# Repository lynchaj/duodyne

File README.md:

# duodyne
* duodyne is a hobbyist retrocomputer system comprised of modules on a system bus.  It is specifically designed to run RomWBW, however, provides support for multiple processor architectures and has a flexible and expandable system bus.

* The system bus is designed to support multiple vintage or retro computer processor architectures such as those from Intel, Zilog, Motorola, Mostek, etc.  The Z80 is the primary CPU used to develop the initial round of peripherals.

* Duodyne borrows heavily from previous computer systems.  The form factor is similar to S-100 and VME.  The bus is electrically is derived from ECB with many extensions to support other processor architectures and improved power distribution.  There are multiple pins for 5V and ground.  +12V and -12V are supported.  3.3V and other values can be derived on board using voltage regulators.

* The plan for the system is to have balance between functionality and complexity.  A single function per board has good distribution and easy expansion but leads to many boards and a large backplane which can lead to electrical and signal distribution issues.  However, full integration into a single board computer reduces complexity somewhat but can make expansion difficult.  

* Duoodyne's bus based approach with a generous board form factor allows for a blend of integration and distribution of two or more functions per board leading to a smaller overall backplane yet retaining flexibility for easy expansion.

* The duodyne core system is defined as an 4-slot or 8-slot backplane, a Z80 or other processor (currently, Z80, 65C816, and TMS9995 are supported), and a ROMRAM board.  The ROMRAM memory board assumes an 8-bit data bus so CPU's with larger data busses may require dedicated memory boards.  The Z80 processor includes a debugging serial port for console access.  The boot ROM is included on the ROMRAM board.

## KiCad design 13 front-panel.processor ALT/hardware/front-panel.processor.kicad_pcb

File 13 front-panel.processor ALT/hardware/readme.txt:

The 4-slot backplane is for the initial prototyping phase of the system.  It can also be used for creating a minimum sized unit.  

The minimum boards for a complete system are: 1) backplane, 2) processor, and 3) ROM & RAM; assumes using processor debug serial port as console

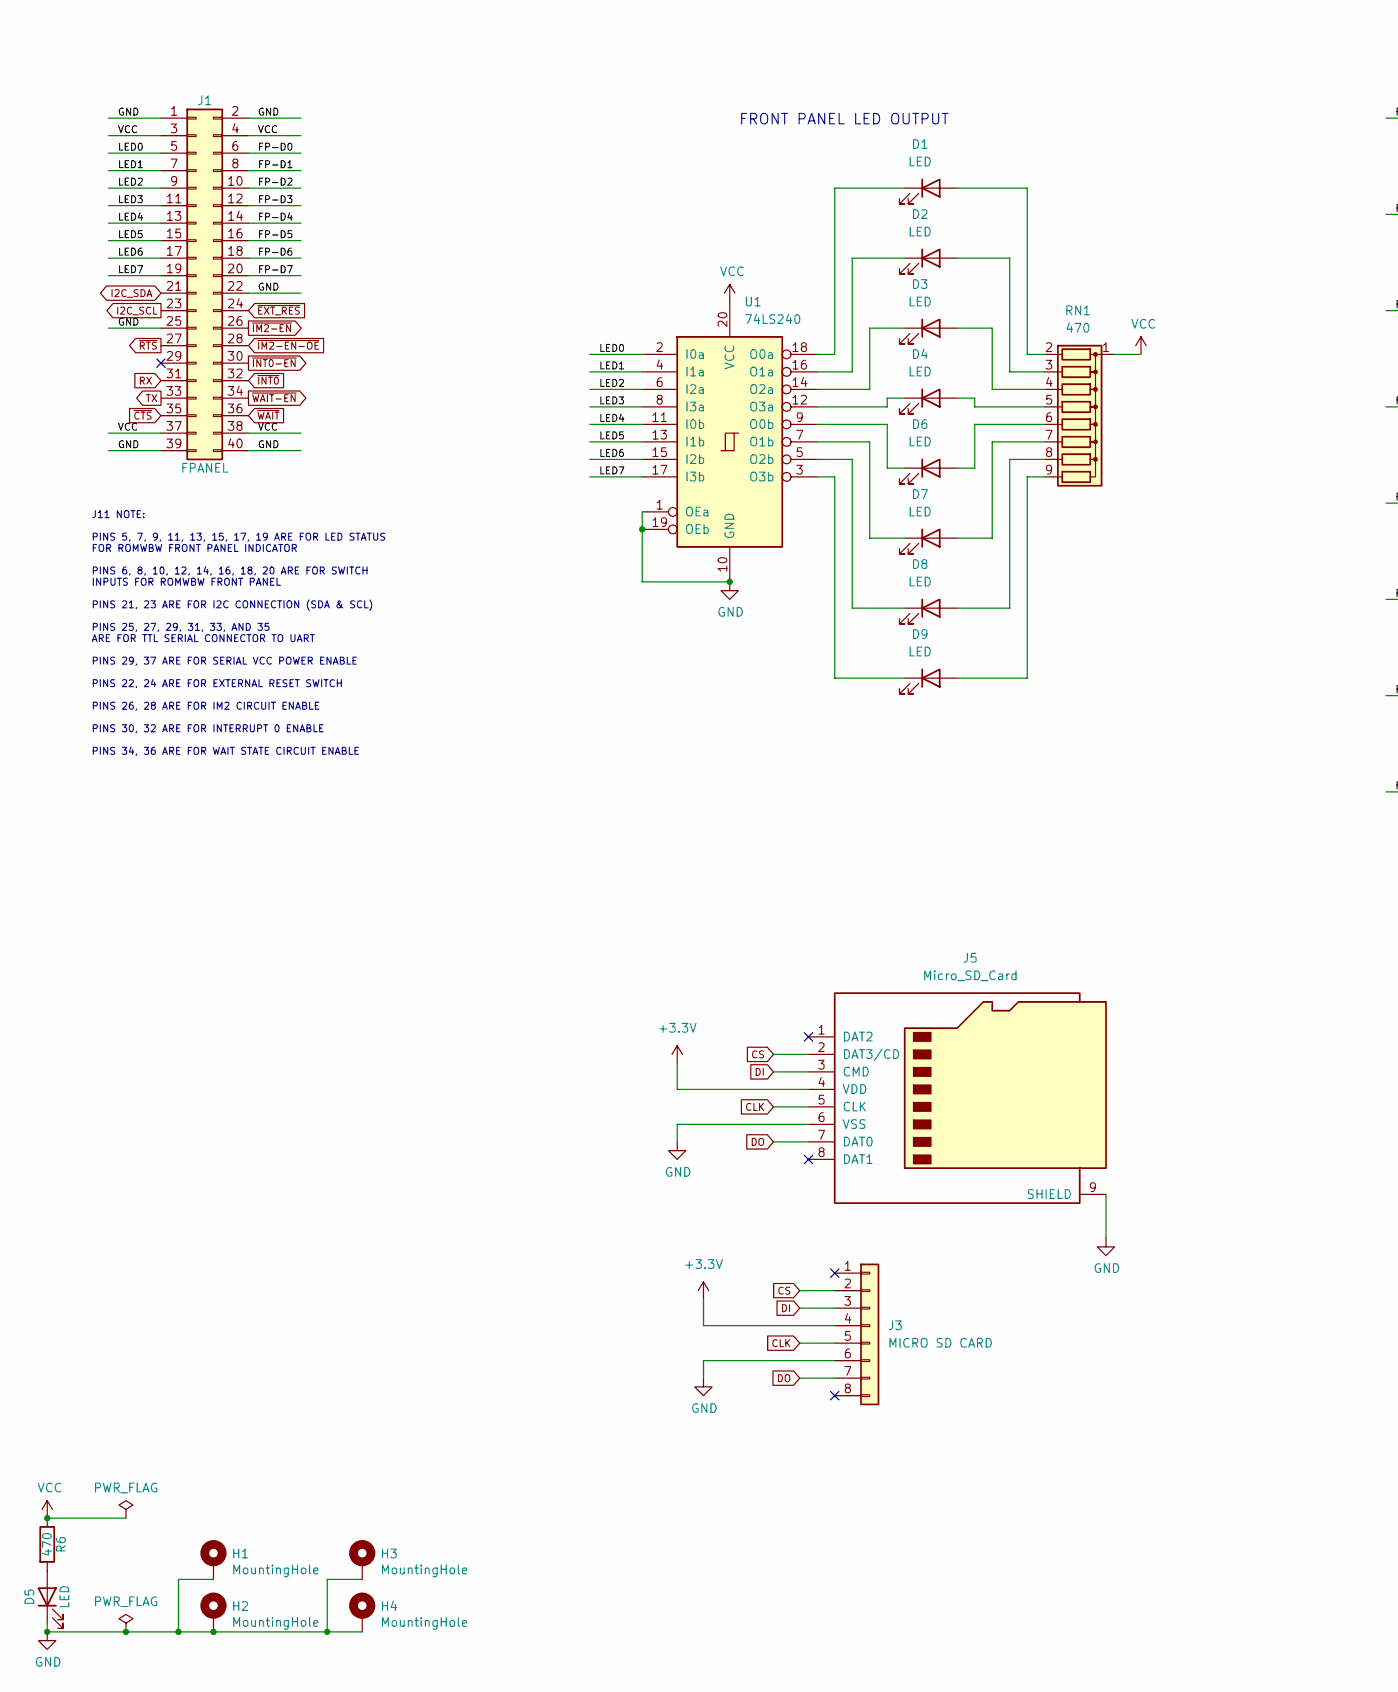
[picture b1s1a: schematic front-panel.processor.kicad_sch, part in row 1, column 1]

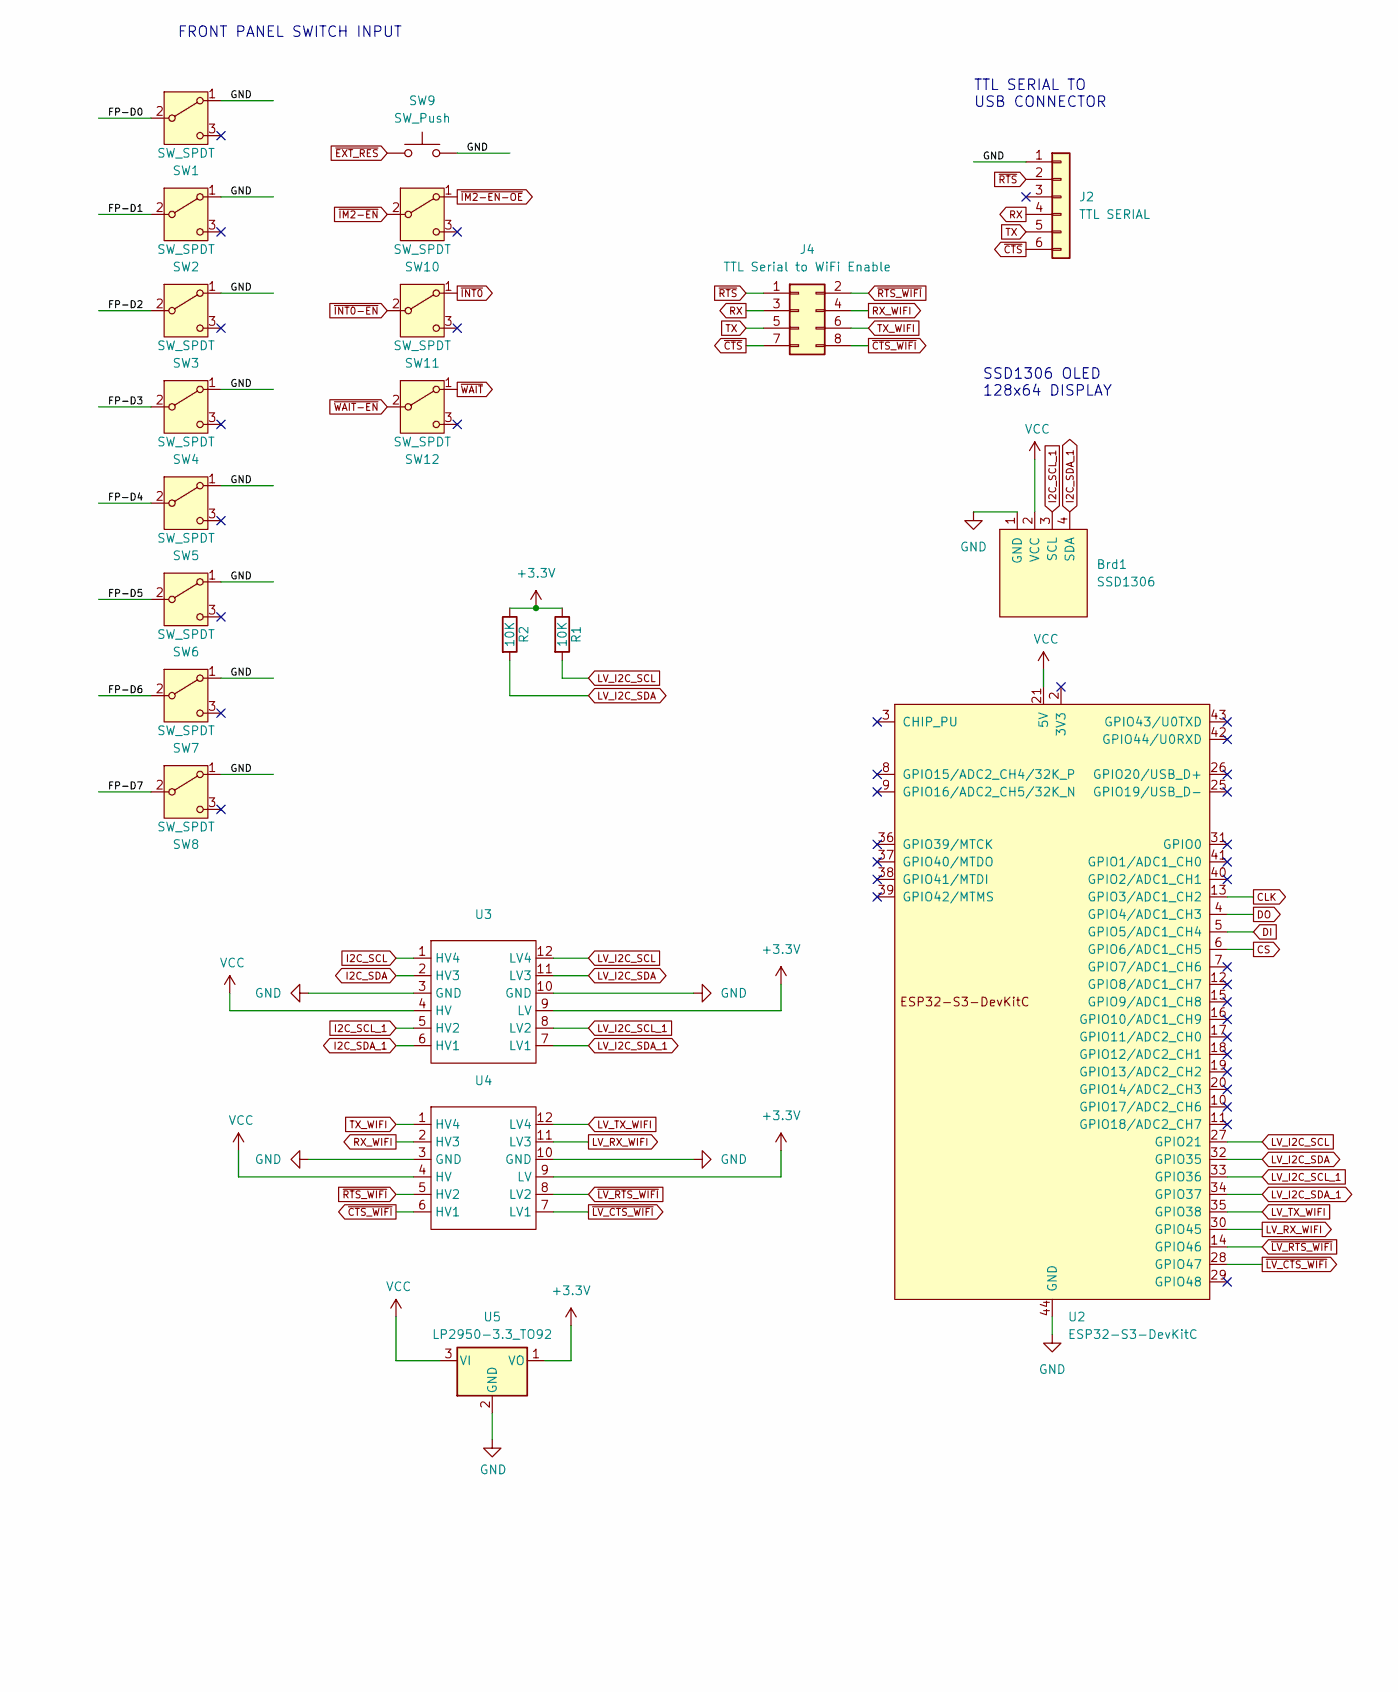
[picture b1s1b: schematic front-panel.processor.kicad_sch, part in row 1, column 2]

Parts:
Brd1: SSD1306; 128x64OLED
D1, D2, D3, D4, D5, D6, D7, D8, D9: LED; LED_D3.0mm
H1, H2, H3, H4: MountingHole; MountingHole_3.2mm_M3_Pad
J1: FPANEL; IDC-Header_2x20_P2.54mm_Horizontal
J2: TTL SERIAL; PinHeader_1x06_P2.54mm_Vertical
J3: MICRO SD CARD; PinSocket_1x08_P2.54mm_Vertical
J4: TTL Serial to WiFi Enable; PinHeader_2x04_P2.54mm_Vertical
J5: Micro_SD_Card; SD_Hirose_DM1AA_SF_PEJ82
R1, R2: 10K; R_Axial_DIN0207_L6.3mm_D2.5mm_P7.62mm_Horizontal
R6: 470; R_Axial_DIN0207_L6.3mm_D2.5mm_P7.62mm_Horizontal
RN1: 470; R_Array_SIP9
SW1, SW2, SW3, SW4, SW5, SW6, SW7, SW8, SW10, SW11, SW12: SW_SPDT; SW_Toggle_Blue_wSlots
SW9: SW_Push; SW_PUSH_6mm
U1: 74LS240; DIP-20_W7.62mm
U2: ESP32-S3-DevKitC; ESP32S3Devkit3Universal
U3, U4: HV-LV
U5: LP2950-3.3_TO92; TO-92_Inline

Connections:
+3.3V: J3.4, J5.4 (VDD), R1.1, R2.1, U3.9 (LV), U4.9 (LV), U5.1 (VO)
/FP-D0: J1.6, SW1.2 (B)
/FP-D1: J1.8, SW2.2 (B)
/FP-D2: J1.10, SW3.2 (B)
/FP-D3: J1.12, SW4.2 (B)
/FP-D4: J1.14, SW5.2 (B)
/FP-D5: J1.16, SW6.2 (B)
/FP-D6: J1.18, SW7.2 (B)
/FP-D7: J1.20, SW8.2 (B)
/LED0: J1.5, U1.2 (I0a)
/LED1: J1.7, U1.4 (I1a)
/LED2: J1.9, U1.6 (I2a)
/LED3: J1.11, U1.8 (I3a)
/LED4: J1.13, U1.11 (I0b)
/LED5: J1.15, U1.13 (I1b)
/LED6: J1.17, U1.15 (I2b)
/LED7: J1.19, U1.17 (I3b)
CLK: J3.5, J5.5 (CLK), U2.13 (GPIO3/ADC1_CH2)
CS: J3.2, J5.2 (DAT3/CD), U2.6 (GPIO6/ADC1_CH5)
DI: J3.3, J5.3 (CMD), U2.5 (GPIO5/ADC1_CH4)
DO: J3.7, J5.7 (DAT0), U2.4 (GPIO4/ADC1_CH3)
GND: Brd1.1 (GND), D5.1 (K), H1.1, H2.1, H3.1, H4.1, J1.1, J1.2, J1.22, J1.25, J1.39, J1.40, J2.1, J3.6, J5.6 (VSS), J5.9 (SHIELD), SW1.1 (A), SW2.1 (A), SW3.1 (A), SW4.1 (A), SW5.1 (A), SW6.1 (A), SW7.1 (A), SW8.1 (A), SW9.2, U1.1 (OEa), U1.10 (GND), U1.19 (OEb), U2.22 (GND), U2.23 (GND), U2.24 (GND), U2.44 (GND), U3.3 (GND), U3.10 (GND), U4.3 (GND), U4.10 (GND), U5.2 (GND)
I2C_SCL: J1.23, U3.1 (HV4)
I2C_SCL_1: Brd1.3 (SCL), U3.5 (HV2)
I2C_SDA: J1.21, U3.2 (HV3)
I2C_SDA_1: Brd1.4 (SDA), U3.6 (HV1)
LV_I2C_SCL: R1.2, U2.27 (GPIO21), U3.12 (LV4)
LV_I2C_SCL_1: U2.33 (GPIO36), U3.8 (LV2)
LV_I2C_SDA: R2.2, U2.32 (GPIO35), U3.11 (LV3)
LV_I2C_SDA_1: U2.34 (GPIO37), U3.7 (LV1)
LV_RX_WIFI: U2.30 (GPIO45), U4.11 (LV3)
LV_TX_WIFI: U2.35 (GPIO38), U4.12 (LV4)
unnamed: D1.2 (A), RN1.2 (R1)
unnamed: D1.1 (K), U1.18 (O0a)
unnamed: D2.2 (A), RN1.3 (R2)
unnamed: D2.1 (K), U1.16 (O1a)
unnamed: D3.2 (A), RN1.4 (R3)
unnamed: D3.1 (K), U1.14 (O2a)
unnamed: D4.2 (A), RN1.5 (R4)
unnamed: D4.1 (K), U1.12 (O3a)
unnamed: D5.2 (A), R6.2
unnamed: D6.2 (A), RN1.6 (R5)
unnamed: D6.1 (K), U1.9 (O0b)
unnamed: D7.2 (A), RN1.7 (R6)
unnamed: D7.1 (K), U1.7 (O1b)
unnamed: D8.2 (A), RN1.8 (R7)
unnamed: D8.1 (K), U1.5 (O2b)
unnamed: D9.2 (A), RN1.9 (R8)
unnamed: D9.1 (K), U1.3 (O3b)
RX: J1.31, J2.4, J4.3
RX_WIFI: J4.4, U4.2 (HV3)
TX: J1.33, J2.5, J4.5
TX_WIFI: J4.6, U4.1 (HV4)
VCC: Brd1.2 (VCC), J1.3, J1.4, J1.37, J1.38, R6.1, RN1.1 (common), U1.20 (VCC), U2.21 (5V), U3.4 (HV), U4.4 (HV), U5.3 (VI)
~CTS_WIFI: J4.8, U4.6 (HV1)
~CTS: J1.35, J2.6, J4.7
~EXT_RES: J1.24, SW9.1
~IM2-EN-OE: J1.28, SW10.1 (A)
~IM2-EN: J1.26, SW10.2 (B)
~INT0-EN: J1.30, SW11.2 (B)
~INT0: J1.32, SW11.1 (A)
~LV_CTS_WIFI: U2.28 (GPIO47), U4.7 (LV1)
~LV_RTS_WIFI: U2.14 (GPIO46), U4.8 (LV2)
~RTS_WIFI: J4.2, U4.5 (HV2)
~RTS: J1.27, J2.2, J4.1
~WAIT-EN: J1.34, SW12.2 (B)
~WAIT: J1.36, SW12.1 (A)

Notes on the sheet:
SSD1306 OLED 128x64 DISPLAY
FRONT PANEL LED OUTPUT
J11 NOTE: PINS 5, 7, 9, 11, 13, 15, 17, 19 ARE FOR LED STATUS FOR ROMWBW FRONT PANEL INDICATOR PINS 6, 8, 10, 12, 14, 16, 18, 20 ARE FOR SWITCH INPUTS FOR ROMWBW FRONT PANEL PINS 21, 23 ARE FOR I2C CONNECTION (SDA & SCL) PINS 25, 27, 29, 31, 33, AND 35 ARE FOR TTL SERIAL CONNECTOR TO UART PINS 29, 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
FRONT PANEL SWITCH INPUT
TTL SERIAL TO USB CONNECTOR

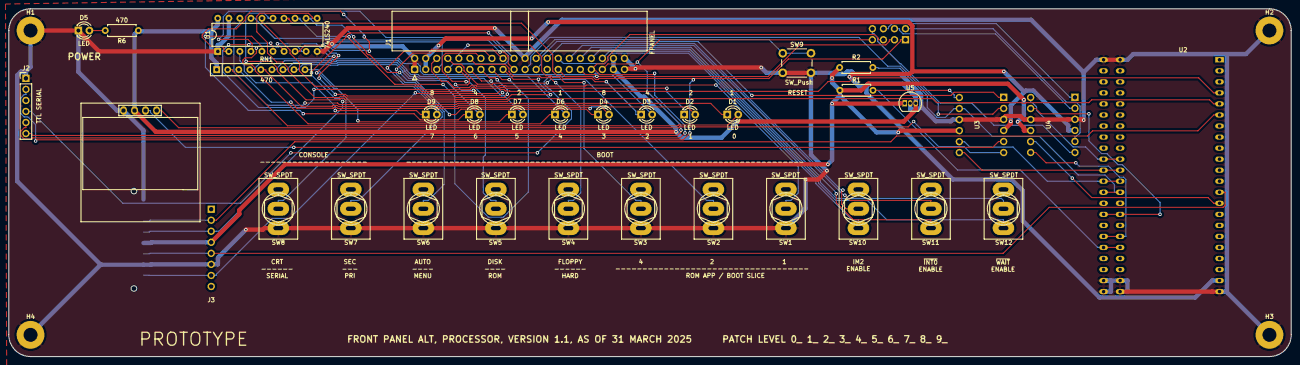
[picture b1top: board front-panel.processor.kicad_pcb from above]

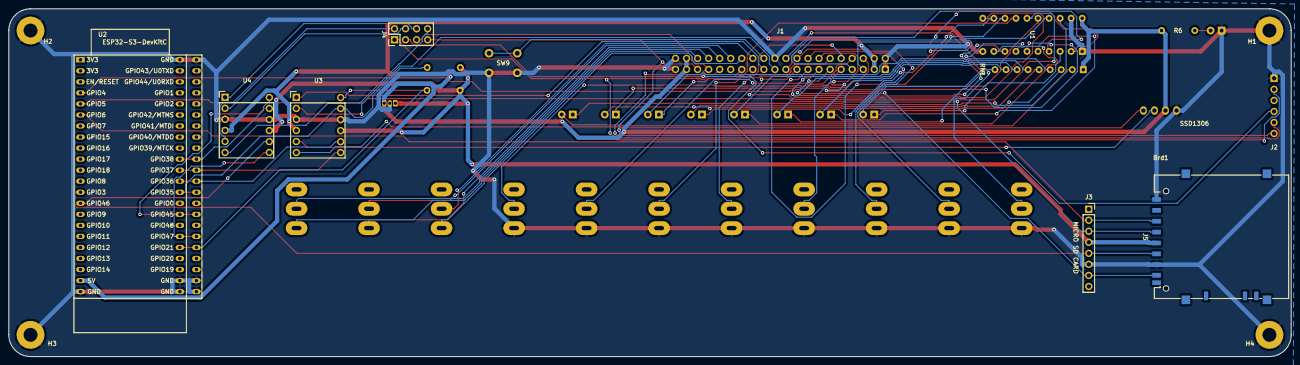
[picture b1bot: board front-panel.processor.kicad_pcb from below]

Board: 2 copper layers, 295.0 x 80.0 mm, 40 parts (6 on the bottom side), 67 nets.

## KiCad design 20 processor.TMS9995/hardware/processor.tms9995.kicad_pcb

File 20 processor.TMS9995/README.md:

# TMS9995 CPU Card

This is a Duodyne implimentation of Stuart Conner's Mini-Cortex system.  The Mini-Cortex system is a further development of his TMS 9995 breadboard project to produce a system similar to a Powertran Cortex, but using more modern components. The system is based around a TMS 9995 running at 3 MHz, with 32K byte EEPROM, and will use 512K bytes of RAM from a Duodyne ROMRAM card accessed through a memory mapper. An on-board serial port and IDE interface exists on the card.

The main EEPROM image provides a boot menu which enables the user to select between the EVMBUG system monitor from TI's TMS 9995 Evaluation Module, a port of the Powertran Cortex Power BASIC made for a TM 990 computer, the Marinchip Disk Executive (MDEX) operating system, and an implementation of V6 Unix including a C compiler.

[Much more information can be found at Stuart's site](https://www.stuartconner.me.uk/mini_cortex/mini_cortex.htm)

[Source code for the Cortex Version of Unix V6 and a ton more TI990 software (including cross development tools) can be found here on Dave Pitts' TI-990 web page.](https://www.cozx.com/dpitts/ti990.html)

## Memory Map
The memory map is shown in the table below.

```
Memory Address	Mapped To
>0000 - >7FFF	ROM when enabled, otherwise RAM
>8000 - >EFFF	RAM
>F000 - >F0FB	TMS 9995 internal RAM
>F0FC - >FDFF	RAM
>FE00 - >FE3F	CF card ATA registers (FIX INCOMPLETE DECODING WITH NEXT REVISION)
>FE40 - >FE7F	Memory mapper registers 0-15 (>FE40 - >FE4F, repeats at >FE50 etc. . .  FIX INCOMPLETE DECODING WITH NEXT REVISION)
>FE80 - >FEBF	Offboard IO (ports $80-$FF)
>FFF0 - >FFF9	RAM
>FFFA - >FFFF	TMS 9995 internal RAM

CRU Address	Mapped To
>0000 - >003F	TMS 9902 registers
>0040 - >007F	Control signal latch (further details here)
 	(Plus processor internal CRU bits)
    
(Note that in TI Speak ">" means Hexidecimal, so for the rest of us >FFFA is the same as $FFFA or 0xFFFA or FFFAH)
```
[for more information see Stuart's site](https://www.stuartconner.me.uk/mini_cortex/mini_cortex.htm)

## Creating CF card Image for MDEX and Unix

The CF card has to be newly formatted with an MBR (master boot record), a single partition formatted as FAT32, and a cluster size of 4096 bytes - the CF card needs to be at least 256 MB to support this. Not all brands/sizes of CF card seem to work - you may have more success with an older, low capacity card. A SanDisk 2.0GB card with a "SDCFB" marking on the back works well.

It can be problematic formatting a new card using Windows 10 as it does not always seem to write an MBR to the card. I use a formatting utility called Rufus [details and download here](https://rufus.ie/en/) with Boot selection==Non bootable, Partition Scheme==MBR, File System=FAT32, and Cluster Size= 4096 Bytes. Once the card is correctly formatted, use Windows to write the four files from the software folder ZIP filedirectly to the card.
[for more information see Stuart's site](https://www.stuartconner.me.uk/mini_cortex/mini_cortex.htm)

## Jumper Settings
```
JP3 - Enable Reset signal from TMS9918 board to go to RES_OUT on bus. closed for Stand Alone Operation, open for secondary CPU

JP1- CPU Signal Pullups - Jumpers should be installed if this is the only CPU card in the system, otherwise leave unjumpered
JP4 - Jumper to enable on board LED for IDE or connect external LED for IDE Activity
JP5 - 2&3 for power on IDE connector 

J4 - Enable Serial Interrupts (required for Unix and MDEX)
J6 - TTL Serial +5v enable
J7 - External User flag bits (CRU 0046-004C)

J2 - 1&2 for Stand Alone Operation, 2&3 for secondary CPU
J3 - 1&2 for Stand Alone Operation, 2&3 for secondary CPU
J8 - 2&3 for Stand Alone Operation, 1&2 for secondary CPU

J9  - Reset Selection -  closed for External bus Reset in 
```
## Powering up
The serial port on the TMS9995 board is configured for 9600 Baud, 7 data bits, even parity, one stop bit, no flow control.

The EVMBUG monitor and Cortex BASIC software applications, and the boot loaders for MDEX and Unix, are stored on a single 32K byte EEPROM. The required application is selected from a boot menu. To display the boot menu, connect the board to a configured serial port on a PC, apply power then press any key.

You should then see:
```
TMS 9995 BREADBOARD SYSTEM
BY STUART CONNER
PRESS 1 FOR EVMBUG MONITOR
PRESS 2 FOR CORTEX BASIC
PRESS 3 FOR MDEX
PRESS 4 FOR UNIX
```
To select a software application from the menu, press the corresponding numeric key.

## Useful Links
MDEX documentation is available on the site http://www.powertrancortex.com/documentation.html. The documentation and MDEX disks were recovered and made available by Dave Hunter, the owner of the www.powertrancortex.com site. Porting of the MDEX files to the Mini-Cortex was by Paul Ruizendaal. On the Mini-Cortex, the files are stored in two emulated disks on the CF card.

The first version of Unix ported was LSX Unix (https://www.mailcom.com/lsx/), which was designed to run with 40K byte RAM and two 256K byte floppies. LSX Unix was adapted from Unix V6 by Dr. Heinz Lycklama (https://www.60bits.net/msu/mycomp/terak/termubel.htm). This port has been further ported to the TI 990 minicomputer by Dave Pitts, who has also made improvements to the code build system.

[Dave Pitts' TI-990 web page.](https://www.cozx.com/dpitts/ti990.html)
[EVMBUG documentation](https://www.stuartconner.me.uk/tibug_evmbug/tibug_evmbug.htm#evmbug)

## Bugs/To Do
* Add Xmodem to Unix
* Add Vi to Unix
* CF card ATA registers have INCOMPLETE DECODING 
* Memory mapper have INCOMPLETE DECODING
* Add Serial port drivers for off board Duodyne hardware
* Add Mass storage drivers for off board Duodyne hardware

## Troubleshooting

The first test image tests just the processor (TMS9995_test_1_eprom_image), the EPROM and the EPROM chip select logic. Program and fit the EPROM, power on, press the reset switch.  The CPU should execute a loop from ROM., then use the logic probe to check for a series of pulses on pin 20 of the EPROM every 2 seconds or so. 

If the first test passes, repeat with the second test image (TMS9995_test_2_eprom_image), which also tests the RAM and the RAM chip select logic. With the second test, a series of pulses should be seen on pin 20 of the EPROM every 6 seconds or so.

The third test image has two versions.   The first version configures the serial port to 9600 Baud, 7 bits/character, even parity, 2 stops bits, no flow control, and then loops continually sending the ASCII characters >21 ("!") to >7E .  This version tests most of the system including ROM and RAM.   The second version is a ROM only version. It also configures the serial port to 9600 Baud, 7 bits/character, even parity, 2 stops bits, no flow control, and then loops continually sending the ASCII characters >21 ("!") to >7E , but does not use any external RAM.

Note that the TMS9995 uses the RAM3 chip on the ROMRAM card, therefore it must be populated for the TMS9995 board to function.

## Patches
   on the .75 Version of the board do not populate R11  
   on the .70 Version of the board, cut pin 3 of RN4 prior to installing and then tie Pin 13 of U11 High

## BOM
Qty|Reference(s)|Value
--- | ----------- | -----
22|C1, C2, C3, C4, C5, C6, C7, C8, C9, C10, C11, C12, C13, C14, C15, C16, C17, C19, C21, C23, C25, C27|0.1u
4|C18, C20, C22, C24|10u
1|C26|22u
1|C28|47uF
2|C40, C41|15pf
1|D1|PWR LED
1|D2|IDLE LED
1|D3|MAP LED
1|D4|1N4148
1|D5|TMS9995 LED
1|D6|IDE ACT LED
1|D7|UART  LED
1|J1|Connector_Generic:Conn_02x08_Odd_Even
1|J2|Connector:Conn_01x03_Male
1|J3|Connector:Conn_01x03_Male
1|J4|Connector:Conn_01x02_Male
1|J5|Connector_Generic:Conn_01x06
1|J6|Connector_Generic:Conn_01x02
1|J7|Connector:Conn_01x06_Male
1|J8|Connector:Conn_01x03_Male
1|J9|Connector_Generic:Conn_01x02
1|JP1|Connector_Generic:Conn_02x04_Odd_Even
1|JP3|Jumper:Jumper_2_Bridged
1|JP4|Jumper:Jumper_2_Open
1|JP5|Connector_Generic:Conn_01x03
3|P1, P2, P3|Connector_Generic:Conn_02x25_Odd_Even
1|P4|Connector_Generic:Conn_02x20_Odd_Even
5|R1, R3, R7, R12, R13|470 ohm
5|R2, R4, R9, R14, R15|10K ohm
2|R5, R10|470 ohm
1|R8|10 ohm
2|RN1, RN2|4700 ohm resistor net (9 pin)
1|RN3|1K ohm resistor net (9 pin)
1|RN4|10K ohm resistor net (9 pin)
1|SW1|Switch:SW_Push
1|U1|74LS14
1|U2|74LS07
1|U3|TMS9995
1|U4|74LS04
2|U5, U7|74LS74
1|U6|74LS112
1|U8|GAL22V10
5|U9, U10, U11, U13, U14|74LS244
1|U12|74LS245
1|U15|74LS138
1|U16|74LS32
2|U17, U20|74LS688
1|U18|27C256
1|U19|DS1233
1|U21|TMS9902A
1|U22|74LS259
1|U23|74LS612
1|U24|74LS08
1|Y1|12MHz crystal

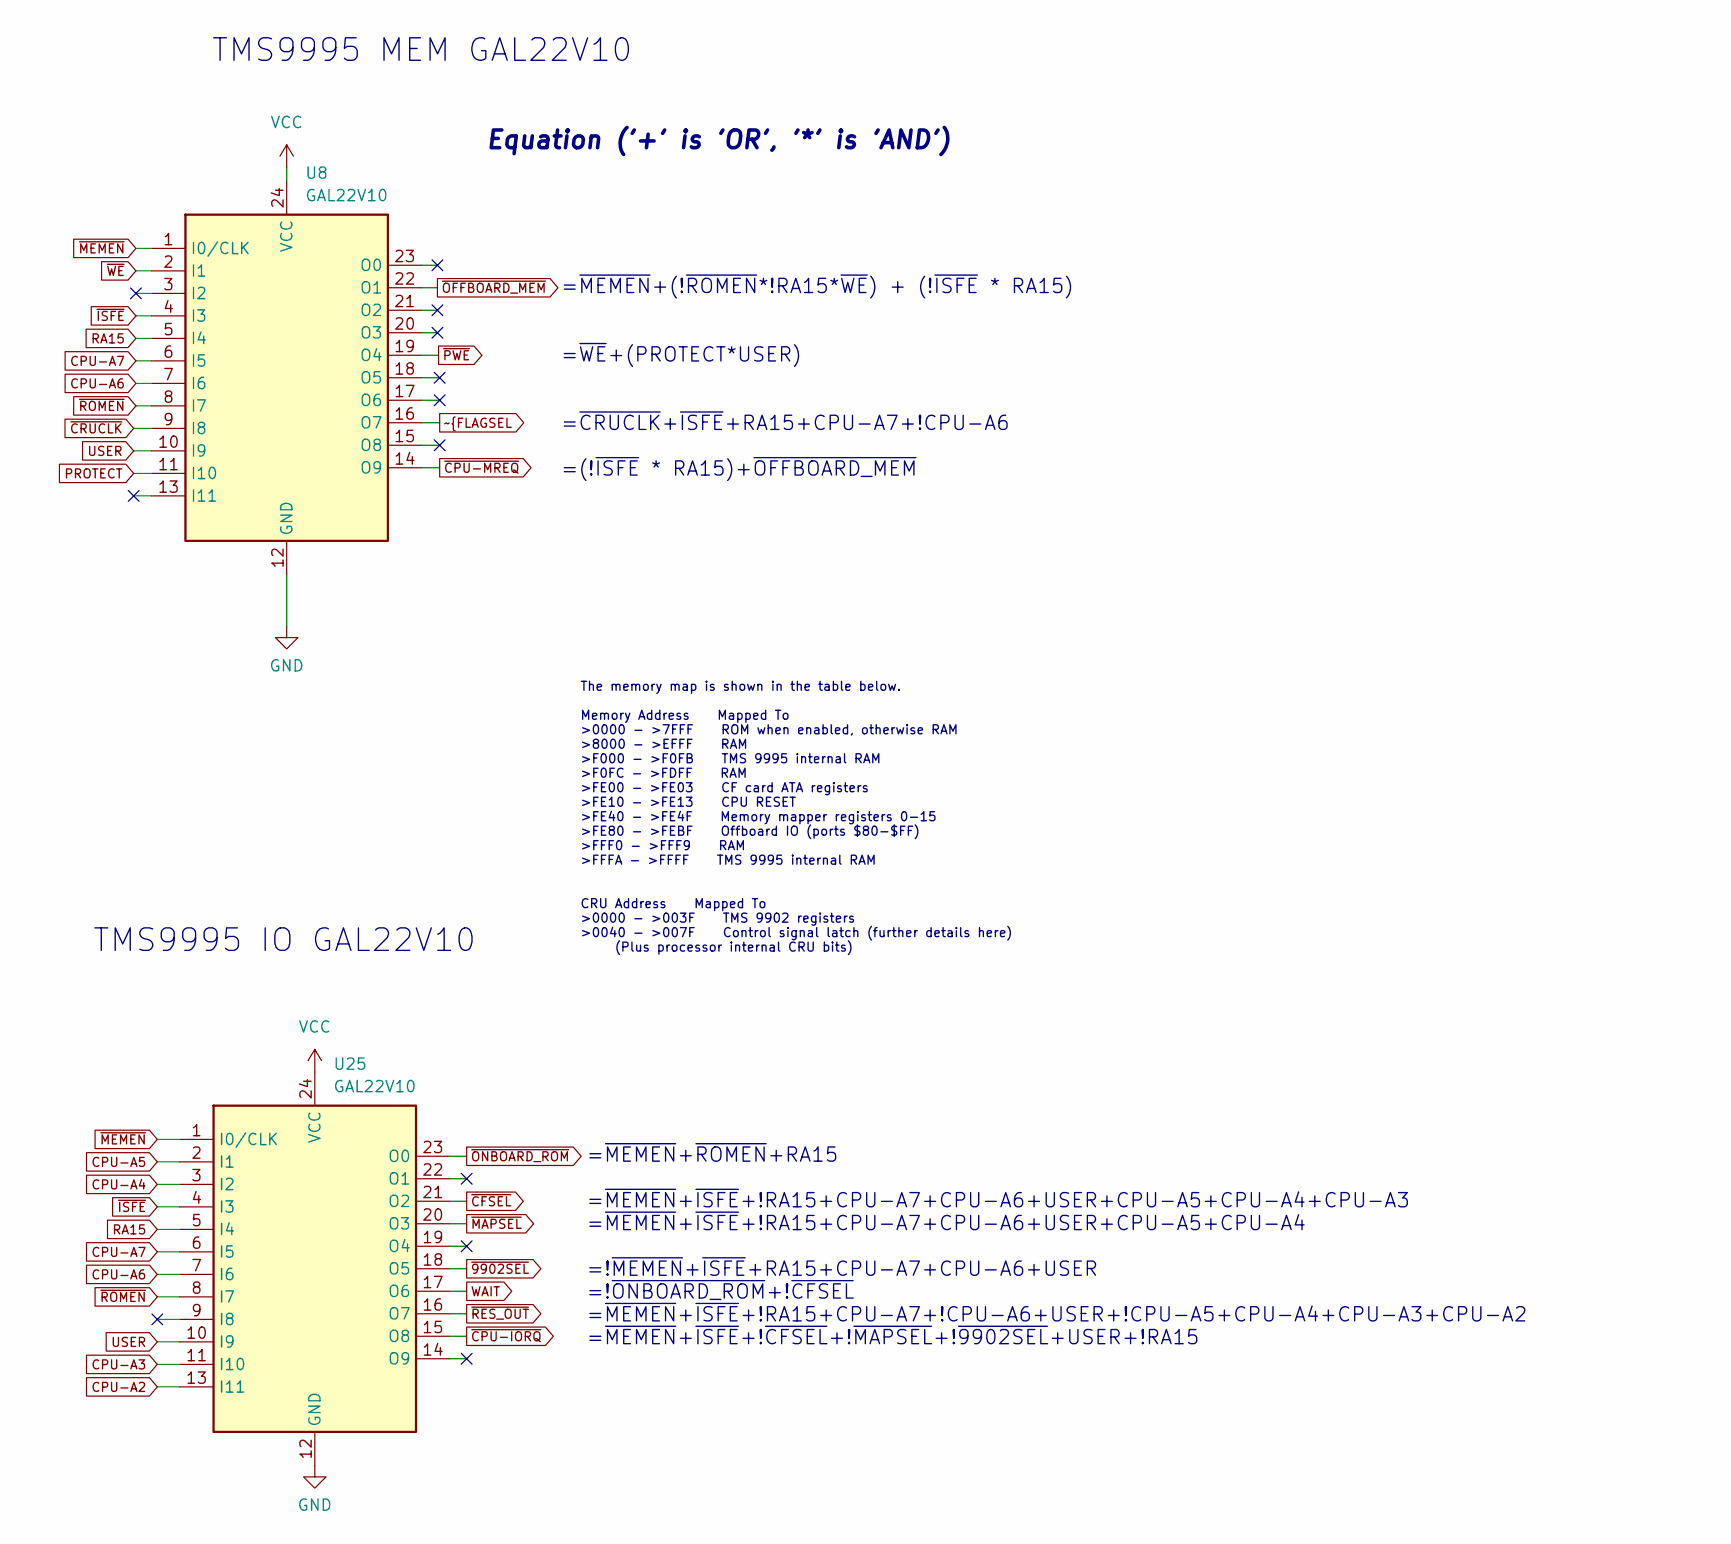
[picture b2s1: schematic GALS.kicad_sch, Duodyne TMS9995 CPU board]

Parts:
U8, U25: GAL22V10; DIP-24_W7.62mm_Socket_LongPads

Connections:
CPU-A2: U25.13 (I11); also elsewhere on the board
CPU-A3: U25.11 (I10); also elsewhere on the board
CPU-A4: U25.3 (I2); also elsewhere on the board
CPU-A5: U25.2 (I1); also elsewhere on the board
CPU-A6: U8.7 (I6), U25.7 (I6); also elsewhere on the board
CPU-A7: U8.6 (I5), U25.6 (I5); also elsewhere on the board
GND: U8.12 (GND), U25.12 (GND); also elsewhere on the board
PROTECT: U8.11 (I10); also elsewhere on the board
RA15: U8.5 (I4), U25.5 (I4); also elsewhere on the board
USER: U8.10 (I9), U25.10 (I9); also elsewhere on the board
VCC: U8.24 (VCC), U25.24 (VCC); also elsewhere on the board
WAIT: U25.17 (O6); also elsewhere on the board
~9902SEL: U25.18 (O5); also elsewhere on the board
~CFSEL: U25.21 (O2); also elsewhere on the board
~CPU-IORQ: U25.15 (O8); also elsewhere on the board
~CPU-MREQ: U8.14 (O9); also elsewhere on the board
~CRUCLK: U8.9 (I8); also elsewhere on the board
~ISFE: U8.4 (I3), U25.4 (I3); also elsewhere on the board
~MAPSEL: U25.20 (O3); also elsewhere on the board
~MEMEN: U8.1 (I0/CLK), U25.1 (I0/CLK); also elsewhere on the board
~OFFBOARD_MEM: U8.22 (O1); also elsewhere on the board
~ONBOARD_ROM: U25.23 (O0); also elsewhere on the board
~PWE: U8.19 (O4); also elsewhere on the board
~ROMEN: U8.8 (I7), U25.8 (I7); also elsewhere on the board
~WE: U8.2 (I1); also elsewhere on the board

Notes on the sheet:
=~{MEMEN}+(!~{ROMEN}*!RA15*~{WE}) + (!~{ISFE} * RA15) =~{WE}+(PROTECT*USER) =~{CRUCLK}+~{ISFE}+RA15+CPU-A7+!CPU-A6 =(!~{ISFE} * RA15)+~{OFFBOARD_MEM}
Equation ('+' is 'OR', '*' is 'AND')
TMS9995 MEM GAL22V10
The memory map is shown in the table below. Memory Address Mapped To >0000 - >7FFF ROM when enabled, otherwise RAM >8000 - >EFFF RAM >F000 - >F0FB TMS 9995 internal RAM >F0FC - >FDFF RAM >FE00 - >FE03 CF card ATA registers >FE10 - >FE13 CPU RESET >FE40 - >FE4F Memory mapper registers 0-15 >FE80 - >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
TMS9995 IO GAL22V10
=~{MEMEN}+~{ROMEN}+RA15 =~{MEMEN}+~{ISFE}+!RA15+CPU-A7+CPU-A6+USER+CPU-A5+CPU-A4+CPU-A3 =~{MEMEN}+~{ISFE}+!RA15+CPU-A7+CPU-A6+USER+CPU-A5+CPU-A4 =!~{MEMEN}+~{ISFE}+RA15+CPU-A7+CPU-A6+USER =!~{ONBOARD_ROM}+!~{CFSEL} =~{MEMEN}+~{ISFE}+!RA15+CPU-A7+!CPU-A6+USER+!CPU-A5+CPU-A4+CPU-A3+CPU-A2 =~{MEMEN}+~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

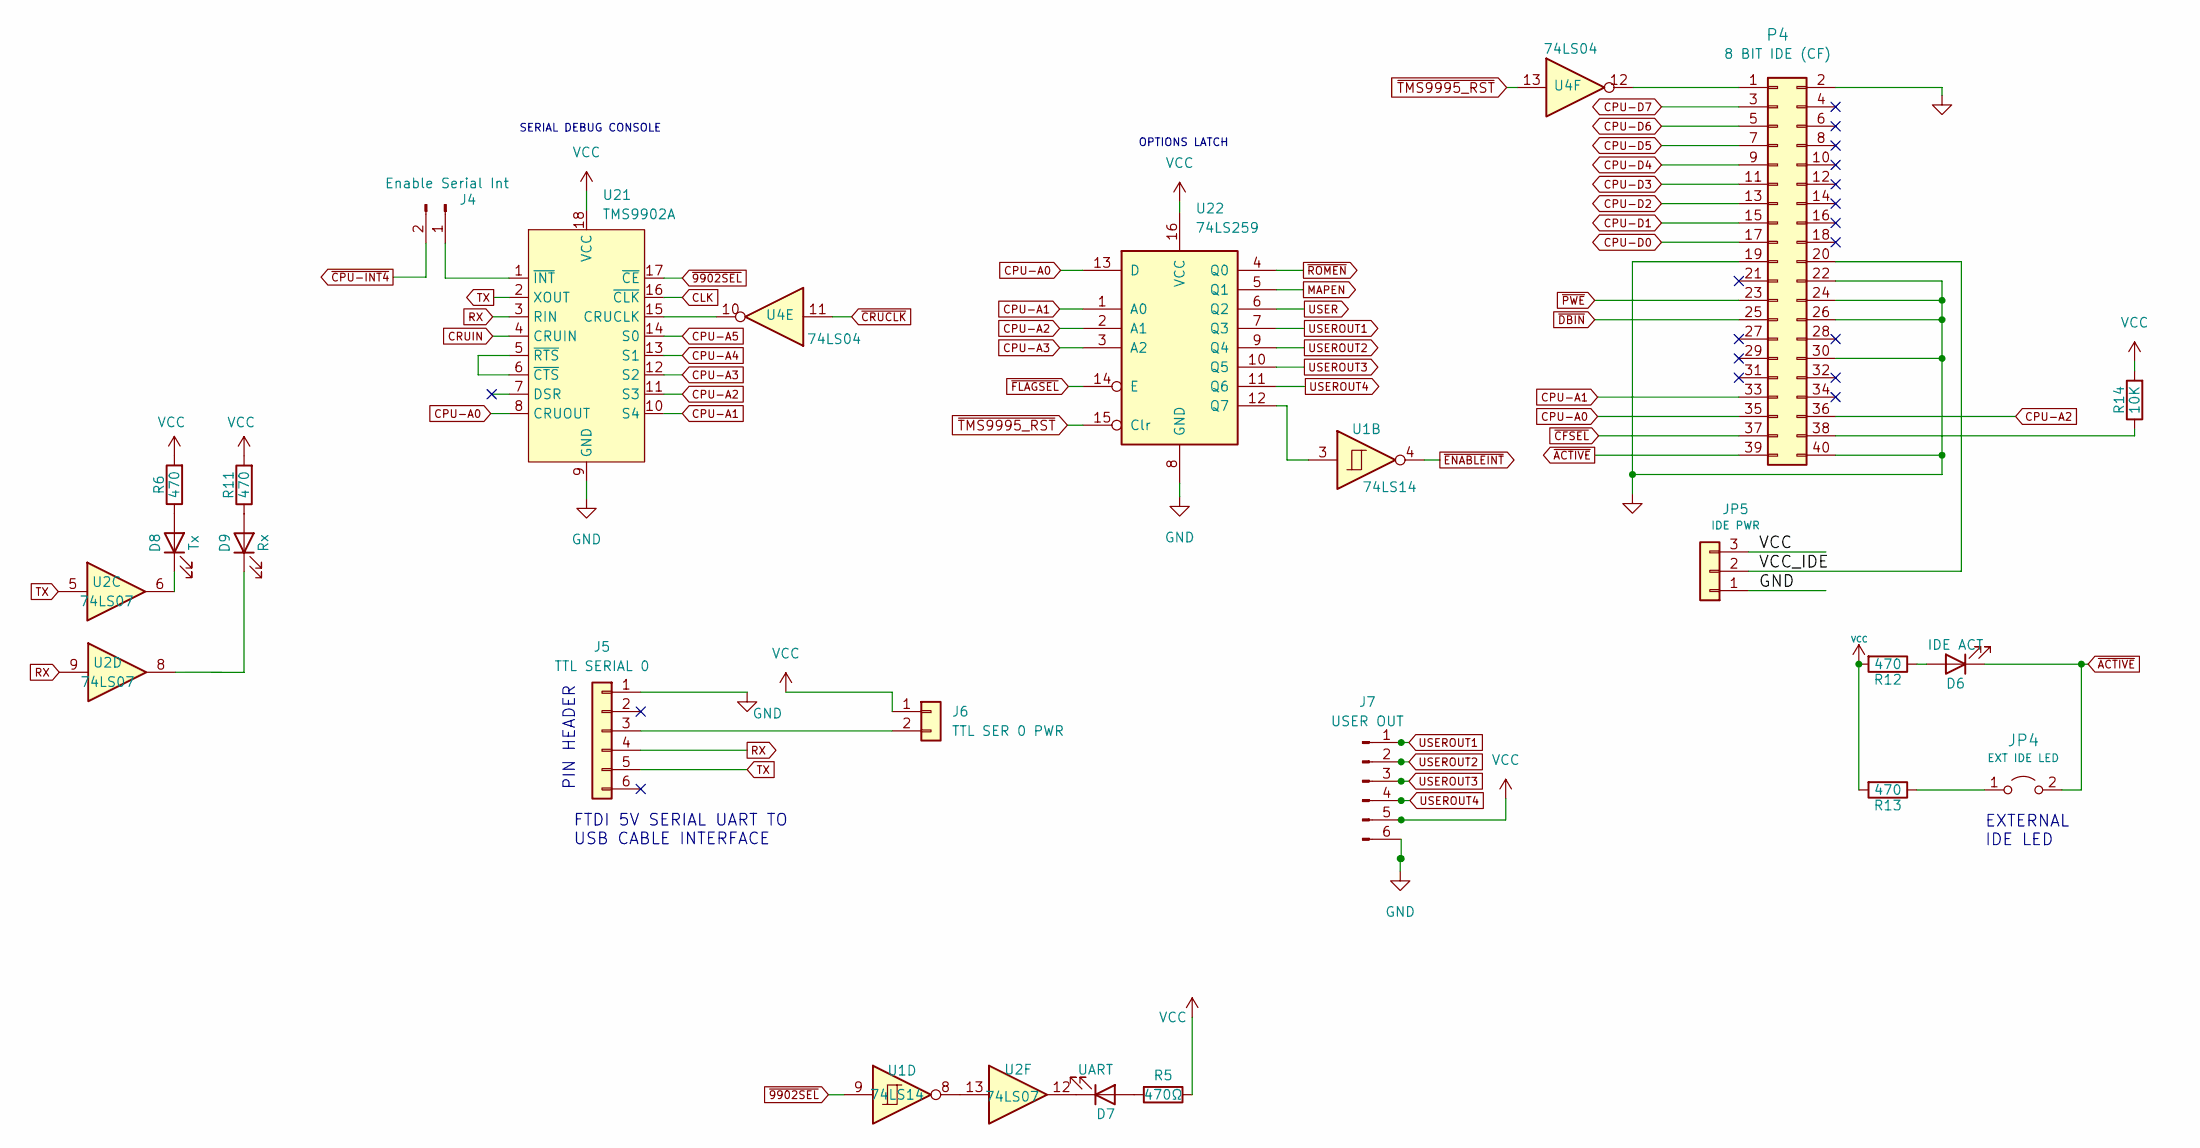
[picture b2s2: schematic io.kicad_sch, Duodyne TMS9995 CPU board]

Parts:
D6: IDE ACT; LED_D3.0mm_Horizontal_O3.81mm_Z2.0mm
D7: UART; LED_D3.0mm_Horizontal_O3.81mm_Z2.0mm
D8: Tx; LED_D3.0mm
D9: Rx; LED_D3.0mm
J4: Enable Serial Int; PinHeader_1x02_P2.54mm_Vertical
J5: TTL SERIAL 0; PinHeader_1x06_P2.54mm_Horizontal
J6: TTL SER 0 PWR; PinHeader_1x02_P2.54mm_Vertical
J7: USER OUT; PinHeader_1x06_P2.54mm_Horizontal
JP4: EXT IDE LED; PinHeader_1x02_P2.54mm_Vertical
JP5: IDE PWR; PinHeader_1x03_P2.54mm_Vertical
P4: 8 BIT IDE (CF); IDC-Header_2x20_P2.54mm_Horizontal
R5: 470Ω; R_Axial_DIN0207_L6.3mm_D2.5mm_P7.62mm_Horizontal
R6, R11, R12, R13: 470; R_Axial_DIN0207_L6.3mm_D2.5mm_P7.62mm_Horizontal
R14: 10K; R_Axial_DIN0207_L6.3mm_D2.5mm_P7.62mm_Horizontal
U1: 74LS14; DIP-14_W7.62mm_Socket_LongPads
U2: 74LS07; DIP-14_W7.62mm_Socket_LongPads
U4: 74LS04; DIP-14_W7.62mm_Socket_LongPads
U21: TMS9902A; DIP-18_W7.62mm_Socket_LongPads
U22: 74LS259; DIP-16_W7.62mm_Socket_LongPads

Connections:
/IO/VCC_IDE: JP5.2, P4.20
CLK: U21.16 (~CLK); also elsewhere on the board
CPU-A0: P4.35, U21.8 (CRUOUT), U22.13 (D); also elsewhere on the board
CPU-A1: P4.33, U21.10 (S4), U22.1 (A0); also elsewhere on the board
CPU-A2: P4.36, U21.11 (S3), U22.2 (A1); also elsewhere on the board
CPU-A3: U21.12 (S2), U22.3 (A2); also elsewhere on the board
CPU-A4: U21.13 (S1); also elsewhere on the board
CPU-A5: U21.14 (S0); also elsewhere on the board
CPU-D0: P4.17; also elsewhere on the board
CPU-D1: P4.15; also elsewhere on the board
CPU-D2: P4.13; also elsewhere on the board
CPU-D3: P4.11; also elsewhere on the board
CPU-D4: P4.9; also elsewhere on the board
CPU-D5: P4.7; also elsewhere on the board
CPU-D6: P4.5; also elsewhere on the board
CPU-D7: P4.3; also elsewhere on the board
CRUIN: U21.4 (CRUIN); also elsewhere on the board
GND: J5.1, J7.6, JP5.1, P4.2, P4.19, P4.22, P4.24, P4.26, P4.30, P4.40, U21.9 (GND), U22.8 (GND); also elsewhere on the board
MAPEN: U22.5 (Q1); also elsewhere on the board
unnamed: D6.2 (A), R12.1
unnamed: D7.1 (K), U2.12
unnamed: D7.2 (A), R5.2
unnamed: D8.1 (K), U2.6
unnamed: D8.2 (A), R6.1
unnamed: D9.1 (K), U2.8
unnamed: D9.2 (A), R11.1
unnamed: J4.1, U21.1 (~INT)
unnamed: J5.3, J6.2
unnamed: JP4.1 (A), R13.1
unnamed: P4.1, U4.12
unnamed: P4.38, R14.1
unnamed: U1.3, U22.12 (Q7)
unnamed: U1.8, U2.13
unnamed: U21.5 (~RTS), U21.6 (~CTS)
unnamed: U4.10, U21.15 (CRUCLK)
RX: J5.4, U2.9, U21.3 (RIN)
TX: J5.5, U2.5, U21.2 (XOUT)
USER: U22.6 (Q2); also elsewhere on the board
USEROUT1: J7.1, U22.7 (Q3)
USEROUT2: J7.2, U22.9 (Q4)
USEROUT3: J7.3, U22.10 (Q5)
USEROUT4: J7.4, U22.11 (Q6)
VCC: J6.1, J7.5, JP5.3, R5.1, R6.2, R11.2, R12.2, R13.2, R14.2, U21.18 (VCC), U22.16 (VCC); also elsewhere on the board
~9902SEL: U1.9, U21.17 (~CE); also elsewhere on the board
~ACTIVE: D6.1 (K), JP4.2 (B), P4.39
~CFSEL: P4.37; also elsewhere on the board
~CPU-INT4: J4.2; also elsewhere on the board
~CRUCLK: U4.11; also elsewhere on the board
~DBIN: P4.25; also elsewhere on the board
~ENABLEINT: U1.4; also elsewhere on the board
~PWE: P4.23; also elsewhere on the board
~ROMEN: U22.4 (Q0); also elsewhere on the board
~TMS9995_RST: U4.13, U22.15 (Clr); also elsewhere on the board

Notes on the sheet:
PIN HEADER
FTDI 5V SERIAL UART TO USB CABLE INTERFACE
EXTERNAL IDE LED
SERIAL DEBUG CONSOLE
OPTIONS LATCH
